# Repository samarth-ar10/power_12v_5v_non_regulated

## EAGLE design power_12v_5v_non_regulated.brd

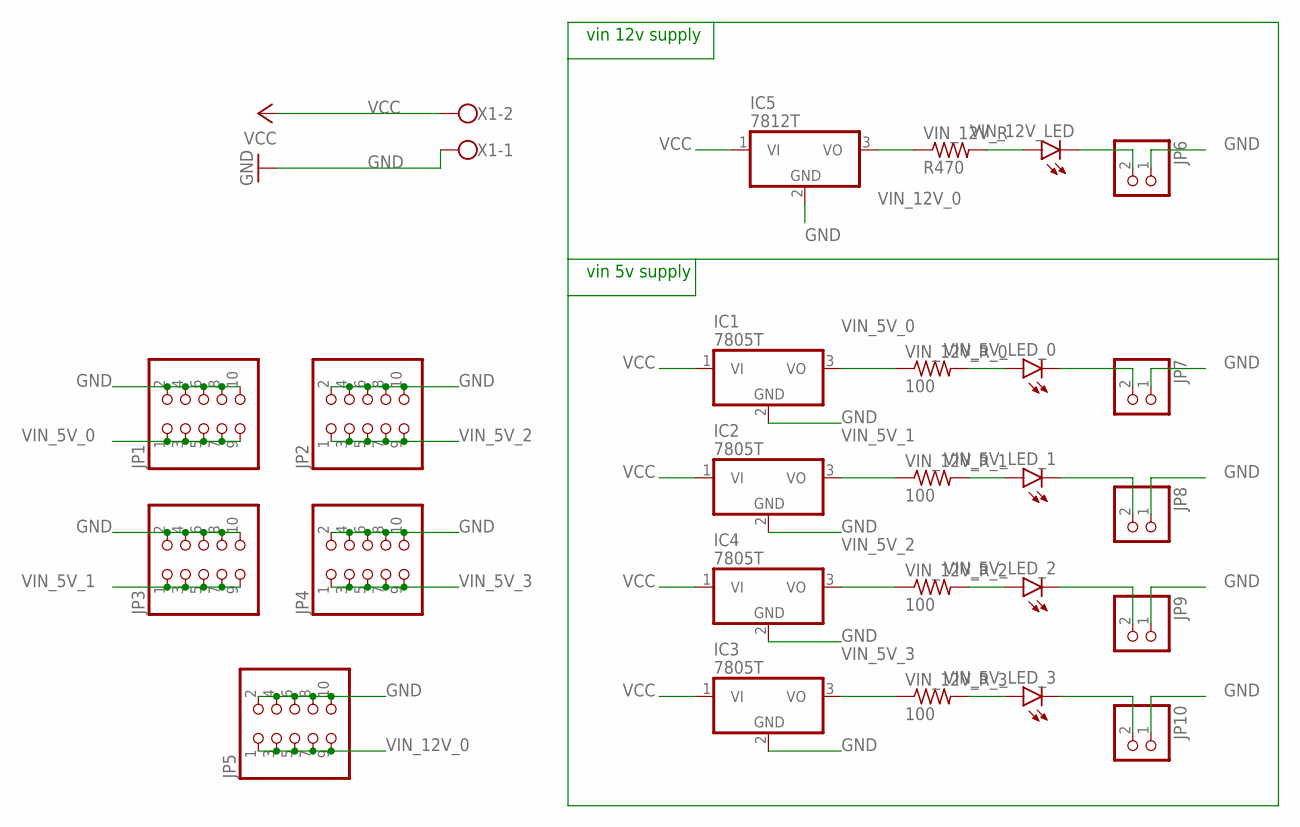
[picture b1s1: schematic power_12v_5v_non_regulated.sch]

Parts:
IC1, IC2, IC3, IC4: 7805T; TO220H
IC5: 7812T; TO220H
JP1, JP2, JP3, JP4, JP5: PINHD-2X5; 2X05
JP6, JP7, JP8, JP9, JP10: PINHD-1X2; 1X02
VIN_5V_LED_0, VIN_5V_LED_1, VIN_5V_LED_2, VIN_5V_LED_3, VIN_12V_LED: LEDSMT1206; 1206
VIN_12V_R: R470; R0805
VIN_12V_R_0, VIN_12V_R_1, VIN_12V_R_2, VIN_12V_R_3: 100; R0805
X1: W237-102

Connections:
GND: IC1.2 (GND), IC2.2 (GND), IC3.2 (GND), IC4.2 (GND), IC5.2 (GND), JP1.2, JP1.4, JP1.6, JP1.8, JP1.10, JP2.2, JP2.4, JP2.6, JP2.8, JP2.10, JP3.2, JP3.4, JP3.6, JP3.8, JP3.10, JP4.2, JP4.4, JP4.6, JP4.8, JP4.10, JP5.2, JP5.4, JP5.6, JP5.8, JP5.10, JP6.1, JP7.1, JP8.1, JP9.1, JP10.1, X1.1
unnamed: VIN_12V_LED.A, VIN_12V_R.2
unnamed: VIN_5V_LED_0.A, VIN_12V_R_0.2
unnamed: VIN_5V_LED_1.A, VIN_12V_R_1.2
unnamed: VIN_5V_LED_2.A, VIN_12V_R_2.2
unnamed: VIN_5V_LED_3.A, VIN_12V_R_3.2
unnamed: JP7.2, VIN_5V_LED_0.C
unnamed: JP6.2, VIN_12V_LED.C
unnamed: JP8.2, VIN_5V_LED_1.C
unnamed: JP9.2, VIN_5V_LED_2.C
unnamed: JP10.2, VIN_5V_LED_3.C
VCC: IC1.1 (VI), IC2.1 (VI), IC3.1 (VI), IC4.1 (VI), IC5.1 (VI), X1.2
VIN_5V_0: IC1.3 (VO), JP1.1, JP1.3, JP1.5, JP1.7, JP1.9, VIN_12V_R_0.1
VIN_5V_1: IC2.3 (VO), JP3.1, JP3.3, JP3.5, JP3.7, JP3.9, VIN_12V_R_1.1
VIN_5V_2: IC4.3 (VO), JP2.1, JP2.3, JP2.5, JP2.7, JP2.9, VIN_12V_R_2.1
VIN_5V_3: IC3.3 (VO), JP4.1, JP4.3, JP4.5, JP4.7, JP4.9, VIN_12V_R_3.1
VIN_12V_0: IC5.3 (VO), JP5.1, JP5.3, JP5.5, JP5.7, JP5.9, VIN_12V_R.1

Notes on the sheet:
vin 5v supply
vin 12v supply

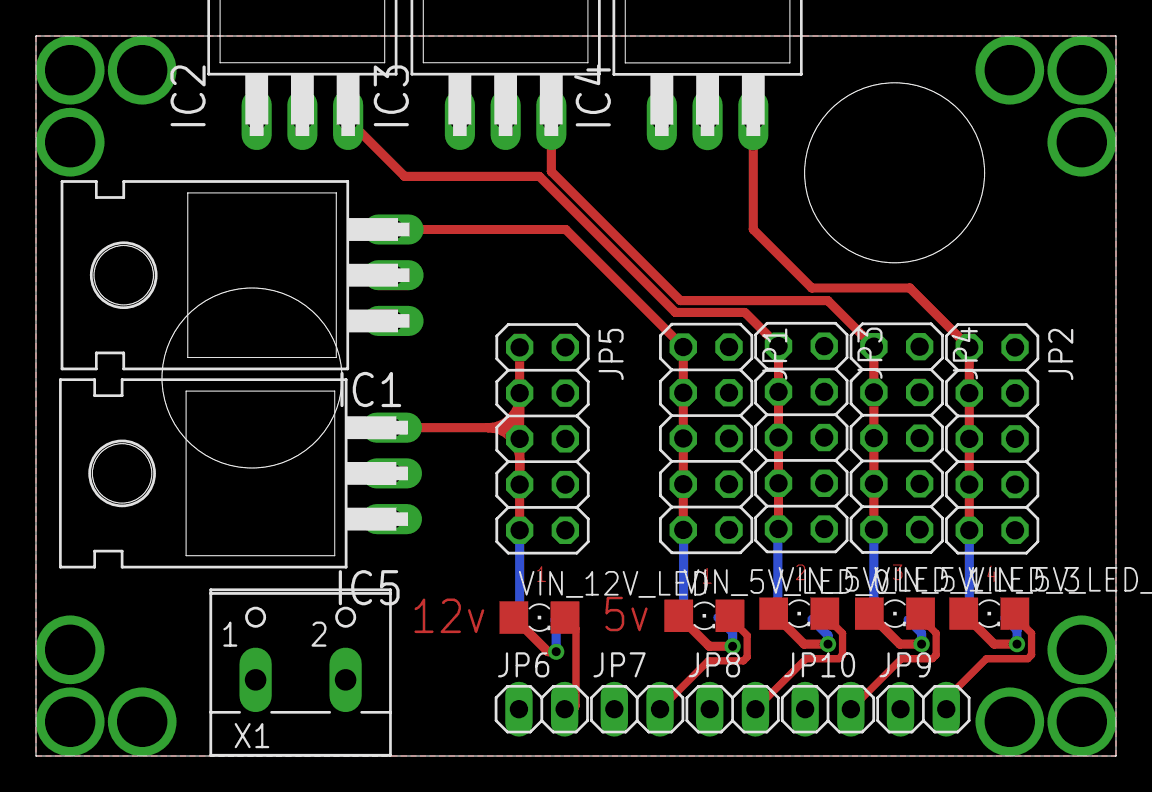
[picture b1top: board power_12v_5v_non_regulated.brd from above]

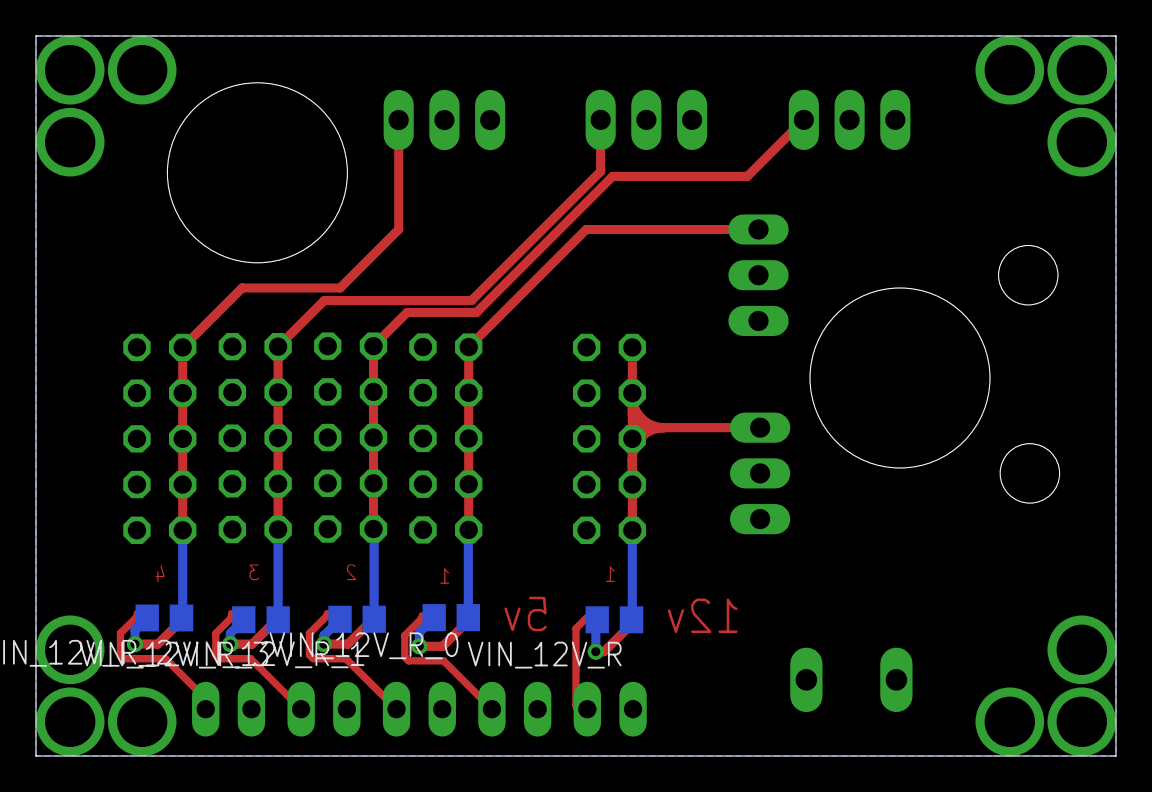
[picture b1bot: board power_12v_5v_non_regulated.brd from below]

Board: 2 copper layers, 60.0 x 40.0 mm, 26 parts (5 on the bottom side), 17 nets.

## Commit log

2020-03-01 pushing files to github
2020-03-15 Adding Images
2020-11-09 adding stl file
